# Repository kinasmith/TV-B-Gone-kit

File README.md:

# TV-B-Gone
### The SMD version

This is a fork of [Adafruit's tv b gone kit](https://github.com/adafruit/TV-B-Gone-kit). I added a lithium charging and protection circuit, and converted the board to be surface mount. It is single-sided and can be made easily on a circuit mill. 

It is tested and works.

## Notes:

avrdude -c avrispmkII -p t85 -B 250 -u -U lfuse:w:0xfd:m -U hfuse:w:0xdf:m

avrdude -c avrispmkII -p t85 -b 19200 -U flash:w:tvbgone.hex:i

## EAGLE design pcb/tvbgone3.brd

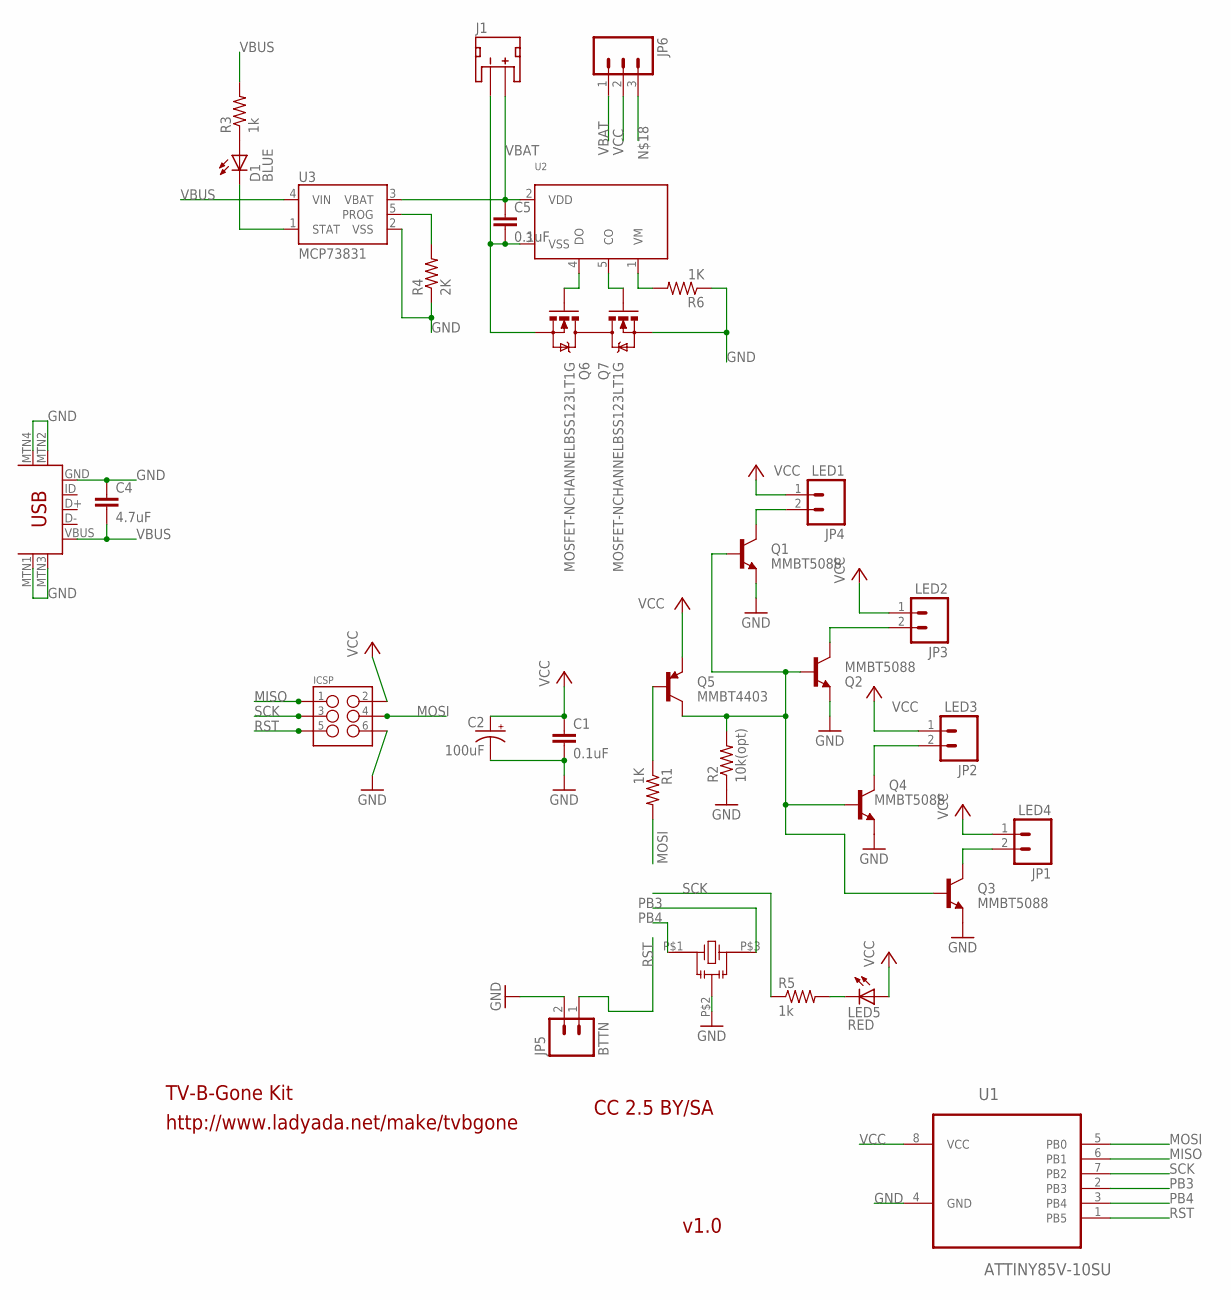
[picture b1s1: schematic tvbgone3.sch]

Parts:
C1, C5: 0.1uF; 0603-CAP
C2: 100uF; PANASONIC_C
C4: 4.7uF; 0603-CAP
D1: BLUE; LED-0603
ICSP: M03X2SMT; 2X3_SMT_POSTS
J1: JST_2MM_MALE; JST-2-SMD
JP1: LED4; 1X02_LONGPADS
JP2: LED3; 1X02_LONGPADS
JP3: LED2; 1X02_LONGPADS
JP4: LED1; 1X02_LONGPADS
JP5: BTTN; 1X02_LONGPADS
JP6: M03SMD_RA_MALE; 1X03_SMD_RA_MALE
LED5: RED; LED-0603
Q1, Q2, Q3, Q4: MMBT5088; SOT23
Q5: MMBT4403; SOT23
Q6, Q7: MOSFET-NCHANNELBSS123LT1G; SOT23
R1, R6: 1K; 0603-RES
R2: 10k(opt); 0603-RES
R3, R5: 1k; 0603-RES
R4: 2K; 0603-RES
U1: ATTINY85V-10SU; SOIC127P798X216-8N
U2: S-8241; SOT23-5L
U3: MCP73831; SOT23-5
U$1: CTSCE8M_00G52; CSTCE
U$2: USB-MINIB-5PIN; USB-MINIB

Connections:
GND: C1.2, C2.-, C4.1, ICSP.6, JP5.2, Q1.2 (E), Q2.2 (E), Q3.2 (E), Q4.2 (E), Q7.2 (S), R2.1, R4.1, R6.1, U1.4 (GND), U3.2 (VSS), U$1.P$2, U$2.GND, U$2.MTN1 (MTN2), U$2.MTN2 (MTN3), U$2.MTN3 (MTN1), U$2.MTN4
MISO: ICSP.1, U1.6 (PB1)
MOSI: ICSP.4, R1.2, U1.5 (PB0)
unnamed: JP4.2, Q1.3 (C)
unnamed: JP3.2, Q2.3 (C)
unnamed: LED5.C, R5.2
unnamed: JP1.2, Q3.3 (C)
unnamed: C5.2, J1.1 (-), Q6.2 (S), U2.3 (VSS)
unnamed: Q5.1 (B), R1.1
unnamed: JP2.2, Q4.3 (C)
unnamed: D1.C, U3.1 (STAT)
unnamed: D1.A, R3.1
unnamed: Q1.1 (B), Q2.1 (B), Q3.1 (B), Q4.1 (B), Q5.3 (C), R2.2
unnamed: R4.2, U3.5 (PROG)
unnamed: Q6.3 (D), Q7.3 (D)
unnamed: Q6.1 (G), U2.4 (DO)
unnamed: Q7.1 (G), U2.5 (CO)
unnamed: R6.2, U2.1 (VM)
PB3: U1.2 (PB3), U$1.P$3
PB4: U1.3 (PB4), U$1.P$1
RST: ICSP.5, JP5.1, U1.1 (PB5)
SCK: ICSP.3, R5.1, U1.7 (PB2)
VBAT: C5.1, J1.2 (+), JP6.1, U2.2 (VDD), U3.3 (VBAT)
VBUS: C4.2, R3.2, U3.4 (VIN), U$2.VBUS
VCC: C1.1, C2.+, ICSP.2, JP1.1, JP2.1, JP3.1, JP4.1, JP6.2, LED5.A, Q5.2 (E), U1.8 (VCC)

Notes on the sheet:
http://www.ladyada.net/make/tvbgone
TV-B-Gone Kit
v1.0
CC 2.5 BY/SA

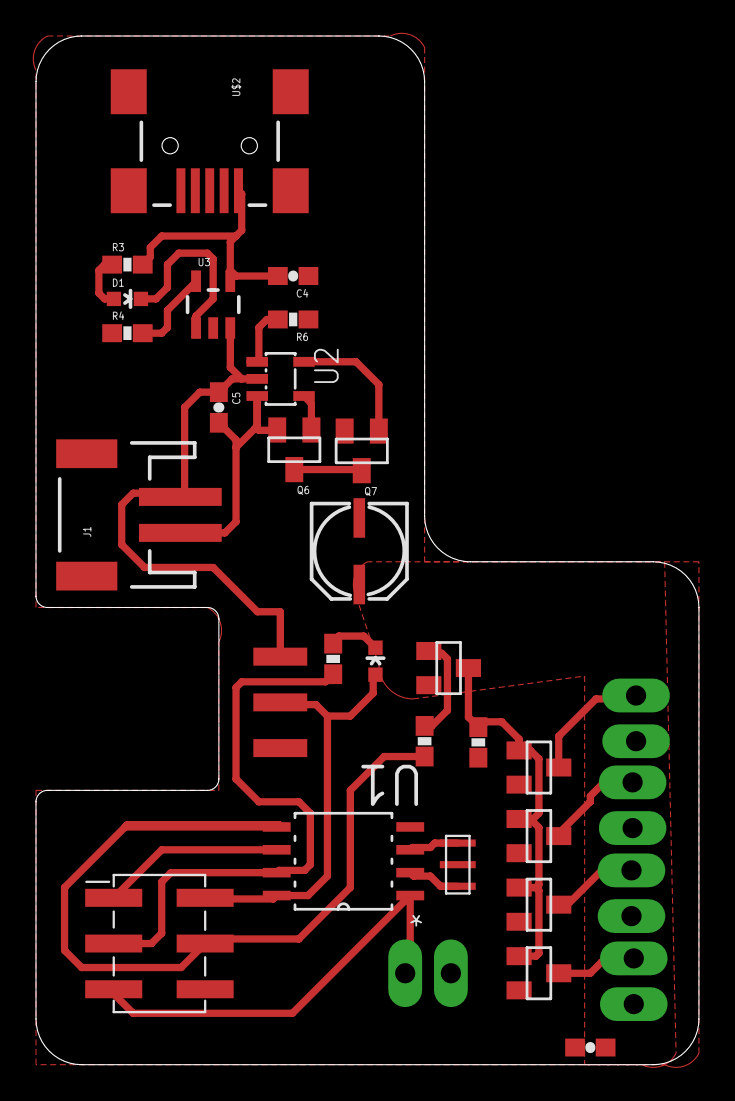
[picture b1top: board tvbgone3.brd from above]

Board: 2 copper layers, 36.8 x 57.1 mm, 32 parts (0 on the bottom side), 25 nets.

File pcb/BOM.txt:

Partlist exported from /Users/kina/Documents/eagle/TV-B-Gone-kit/pcb/tvbgone3.sch at 2/15/15 9:57 AM

Part Value                     Device                    Package            Description                                                                             
C1   0.1uF                     0.1UF-25V-5%(0603)        0603-CAP           CAP-08604                                                                               
C2   100uF                     CAP_POLC                  PANASONIC_C        Capacitor Polarized                                                                     
C4   4.7uF                     0.22UF50V-20%,+80%(0603)  0603-CAP           CAP-09885                                                                               
C5   0.1uF                     0.22UF50V-20%,+80%(0603)  0603-CAP           CAP-09885                                                                               
D1   BLUE                      LED-BLUE0603              LED-0603           Blue LEDs for production use                                                            
ICSP                           M03X2SMT                  2X3_SMT_POSTS      2x3 .1" header.                                                                         
J1                             JST_2MM_MALE              JST-2-SMD          Mates to single-cell LiPo batteries.                                                    
JP1  LED4                      M02PTH3                   1X02_LONGPADS      Standard 2-pin 0.1" header. Use with                                                    
JP2  LED3                      M02PTH3                   1X02_LONGPADS      Standard 2-pin 0.1" header. Use with                                                    
JP3  LED2                      M02PTH3                   1X02_LONGPADS      Standard 2-pin 0.1" header. Use with                                                    
JP4  LED1                      M02PTH3                   1X02_LONGPADS      Standard 2-pin 0.1" header. Use with                                                    
JP5  BTTN                      M02PTH3                   1X02_LONGPADS      Standard 2-pin 0.1" header. Use with                                                    
JP6                            M03SMD_RA_MALE            1X03_SMD_RA_MALE   Header 3                                                                                
LED5 RED                       LED0603                   LED-0603           LEDs                                                                                    
Q1   MMBT5088                  TRANSISTOR_NPNMMBT5088    SOT23              Generic NPN BJT                                                                         
Q2   MMBT5088                  TRANSISTOR_NPNMMBT5088    SOT23              Generic NPN BJT                                                                         
Q3   MMBT5088                  TRANSISTOR_NPNMMBT5088    SOT23              Generic NPN BJT                                                                         
Q4   MMBT5088                  TRANSISTOR_NPNMMBT5088    SOT23              Generic NPN BJT                                                                         
Q5   MMBT4403                  TRANSISTOR_PNPMMBT4403    SOT23              Generic PNP BJT                                                                         
Q6   MOSFET-NCHANNELBSS123LT1G MOSFET-NCHANNELBSS123LT1G SOT23              Common NMOSFET Parts                                                                    
Q7   MOSFET-NCHANNELBSS123LT1G MOSFET-NCHANNELBSS123LT1G SOT23              Common NMOSFET Parts                                                                    
R1   1K                        2MOHMS-1/10W-1%(0603)     0603-RES           RES-10054                                                                               
R2   10k(opt)                  2MOHMS-1/10W-1%(0603)     0603-RES           RES-10054                                                                               
R3   1k                        3.3MOHM-1/10W-1%(0603)    0603-RES           RES-11057                                                                               
R4   2K                        3.3MOHM-1/10W-1%(0603)    0603-RES           RES-11057                                                                               
R5   1k                        2MOHMS-1/10W-1%(0603)     0603-RES           RES-10054                                                                               
R6   1K                        3.3MOHM-1/10W-1%(0603)    0603-RES           RES-11057                                                                               
U$1  CTSCE8M_00G52             CTSCE8M_00G52             CSTCE                                                                                                      
U$2  USB-MINIB-5PIN            USB-MINIB-5PIN            USB-MINIB          Mini-USB "B" connector with 5th pin broken out.                                         
U1   ATTINY85V-10SU            ATTINY85V-10SU            SOIC127P798X216-8N 8-bit Microcontroller with In-System Programmable Flash                                 
U2                             S-8241                    SOT23-5L           Seiko S-8241                                                                            
U3   MCP73831                  MCP73831                  SOT23-5            Miniature single cell, fully integrated Li-Ion, Li-polymer charge management controller

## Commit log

2015-02-15 version 1 of the new board design done
2015-02-15 finalized version 1 of smd board and documented the fuses. Tested. It Works\!
2015-02-15 fixed last commit, oops

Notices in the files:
parts and their libraries:
SparkFun-DiscreteSemi: Licensing: CC v3.0 Share-Alike You are welcome to use this library for commercial purposes.
